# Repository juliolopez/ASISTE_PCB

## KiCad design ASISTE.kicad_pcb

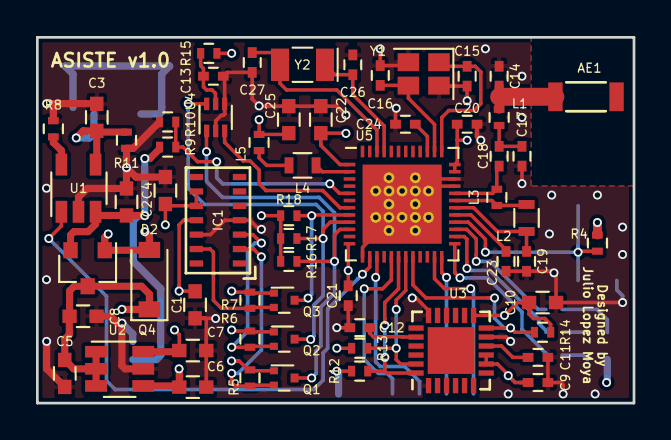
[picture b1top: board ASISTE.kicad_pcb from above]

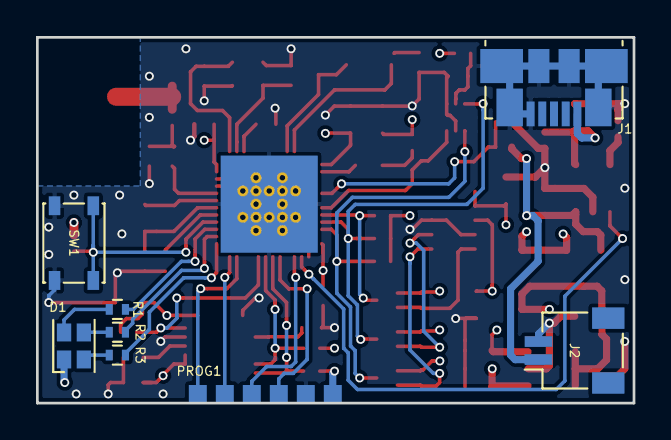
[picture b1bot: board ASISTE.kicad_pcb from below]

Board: 4 copper layers, 33.1 x 20.3 mm, 69 parts (8 on the bottom side), 46 nets.

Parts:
AE1: Antenna_Chip; ANT
C1, C3, C4, C22: C_0603_4.7uF; C_0603
C2: C_0603_10uF; C_0603
C5, C6, C7, C8, C25: C_0603_1uF; C_0603
C9, C11, C13, C21, C24: C_0402_100nF; C_0402
C10: C_0603_10nF; C_0603
C12, C19: C_0402_2.2nF; C_0402
C14: C_0402_1.5pF; C_0402
C15, C16, C26, C27: C_0402_12pF; C_0402
C17: C_0402_1pF; C_0402
C18: C_0402_2.2pF; C_0402
C20: C_0402_1nF; C_0402
C23: C_0402_47nF; C_0402
D1: LED_ARGB; LED_Cree-PLCC4_2x2mm_CW
D2: D_Schottky; D_SOD-123
IC1: MAX30105; Maxim_OLGA-14_3.3x5.6mm_P0.8mm
J1: USB_B_Micro_SMD; USB_Micro-B_Molex_47346-0001
J2: Conn_01x02; JST_SH_SM02B-SRSS-TB_1x02-1MP_P1.00mm_Horizontal
L1: L_0402_3.3nH; L_0402
L2: L_0603_10nH; L_0603
L3: L_0402_4.7nH; L_0402
L4: L_0603_10uH; L_0603
L5: L_0402_15nH; L_0402
PROG1: SMD_01x06; SMD_PROG
Q1, Q2, Q3: NTK3134NT1G; SOT-723
Q4: DMP1045U; SOT-23
R1, R2: R_0402_33; R_0402
R3, R4: R_0402_100; R_0402
R5, R6, R7, R12, R13, R16, R17, R18: R_0402_10k; R_0402
R8: R_0402_2k; R_0402
R9: R_0402_10M; R_0402
R10: R_0402_2M2; R_0402
R11, R14: R_0402_100k; R_0402
R15: R_0402_4k7; R_0402
SW1: SW_SPST; SW_SPST_PTS810
U1: MCP73831; TSOT-23-5
U2: XC6415CC91MR-G; TSOT-23-6
U3: MPU-6050; QFN-24-1EP_4x4mm_Pitch0.5mm
U4: TMP112AIDRLR; SOT-563
U5: nRF51x22-QFxx; QFN-48-1EP_6x6mm_Pitch0.4mm_ThermalVias
Y1: Crystal_GND24_2520; Crystal_SMD_2520-4pin_2.5x2.0mm
Y2: Crystal_3.2x1.5; Crystal_SMD_G8-2Pin_3.2x1.5mm

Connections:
+1V8: C1.1, C7.1, IC1.11, Q1.1, Q2.1, Q3.1, R5.1, R6.2, R7.1, U2.6
+3V3: C2.2, C6.1, C9.1, C10.2, C20.1, C21.1, C22.1, C25.2, D1.1, IC1.9, IC1.10, L5.2, PROG1.1, R4.1, R12.1, R13.1, R14.1, R15.1, R16.1, R17.1, R18.1, U2.4, U3.8, U3.9, U3.13, U5.1, U5.12, U5.35, U5.36
/heartRate/HR_SCL: Q1.3, R16.2, U4.1, U5.10
/heartRate/HR_SDA: Q2.3, R17.2, U4.6, U5.9
/heartRate/HR_~INT: Q3.3, R18.2, U5.8
/imu/IMU_INT: R14.2, U3.12, U5.20
/imu/IMU_SCL: R13.2, U3.23, U5.19
/imu/IMU_SDA: R12.2, U3.24, U5.18
/micro/BAT_CHG_STAT: U1.1, U5.14
/micro/BAT_SENSE: R9.2, R10.1, U5.5
/micro/BUTTON: R4.2, SW1.1, U5.28
/micro/LED_BLUE: R1.2, U5.27
/micro/LED_GREEN: R2.2, U5.26
/micro/LED_RED: R3.2, U5.25
/micro/MCU_DEBUG_SWCLK: PROG1.5, U5.24
/micro/MCU_DEBUG_SWDIO: PROG1.6, U5.23
/micro/MCU_PROG_RX: PROG1.4, U5.15
/micro/MCU_PROG_TX: PROG1.3, U5.17
/micro/TMP_ALERT: U4.3, U5.7
GND: C1.2, C2.1, C3.1, C4.2, C5.2, C6.2, C7.2, C8.2, C9.2, C10.1, C11.2, C12.2, C13.2, C14.2, C15.2, C16.2, C17.1, C19.2, C20.2, C21.2, C22.2, C23.2, C24.2, C25.1, C26.1, C27.1, IC1.4, IC1.12, J1.5, J1.6, J2.2, PROG1.2, R8.2, R10.2, R11.2, SW1.2, U1.2, U2.5, U3.1, U3.11, U3.18, U4.2, U4.4, U5.13, U5.33, U5.34, U5.49, Y1.2, Y1.4
unnamed: AE1.1, C14.1, L1.1
unnamed: C11.1, U3.10
unnamed: C12.1, U3.20
unnamed: C13.1, R15.2, U4.5
unnamed: C15.1, U5.37, Y1.1
unnamed: C16.1, U5.38, Y1.3
unnamed: C17.2, C18.1, L1.2
unnamed: C18.2, L3.2, U5.32
unnamed: C19.1, L2.1, U5.30
unnamed: C23.1, U5.29
unnamed: C24.1, U5.39
unnamed: C26.2, U5.45, Y2.1
unnamed: C27.2, U5.46, Y2.2
unnamed: D1.2, R1.1
unnamed: D1.3, R2.1
unnamed: D1.4, R3.1
unnamed: IC1.2, Q1.2, R5.2
unnamed: IC1.3, Q2.2, R6.1
unnamed: IC1.13, Q3.2, R7.2
unnamed: L2.2, L3.1, U5.31
unnamed: L4.1, U5.2
unnamed: L4.2, L5.1
unnamed: R8.1, U1.5
VBAT: C4.1, J2.1, Q4.2, R9.1, U1.3
VBUS: C3.2, D2.2, J1.1, Q4.1, R11.1, U1.4
VCC: C5.1, C8.1, D2.1, Q4.3, U2.1, U2.2, U2.3

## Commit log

2018-07-13 primer commit
2018-08-20 Esquemático a falta de incluir el conversor DC/DC
2018-08-29 Terminado esquemático. Falta revisar
2018-08-29 Esquemático parcialmente revisado. Falta revisar pines y correspondencia con footprints
2018-09-05 Añadido botón y otros
2018-09-12 Esquemáticos totalmente terminados y revisados PCB a falta de routear el puerto de programación
2018-09-17 Actualizando
